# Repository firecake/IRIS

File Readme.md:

This is a try to build an open source spectrometer...

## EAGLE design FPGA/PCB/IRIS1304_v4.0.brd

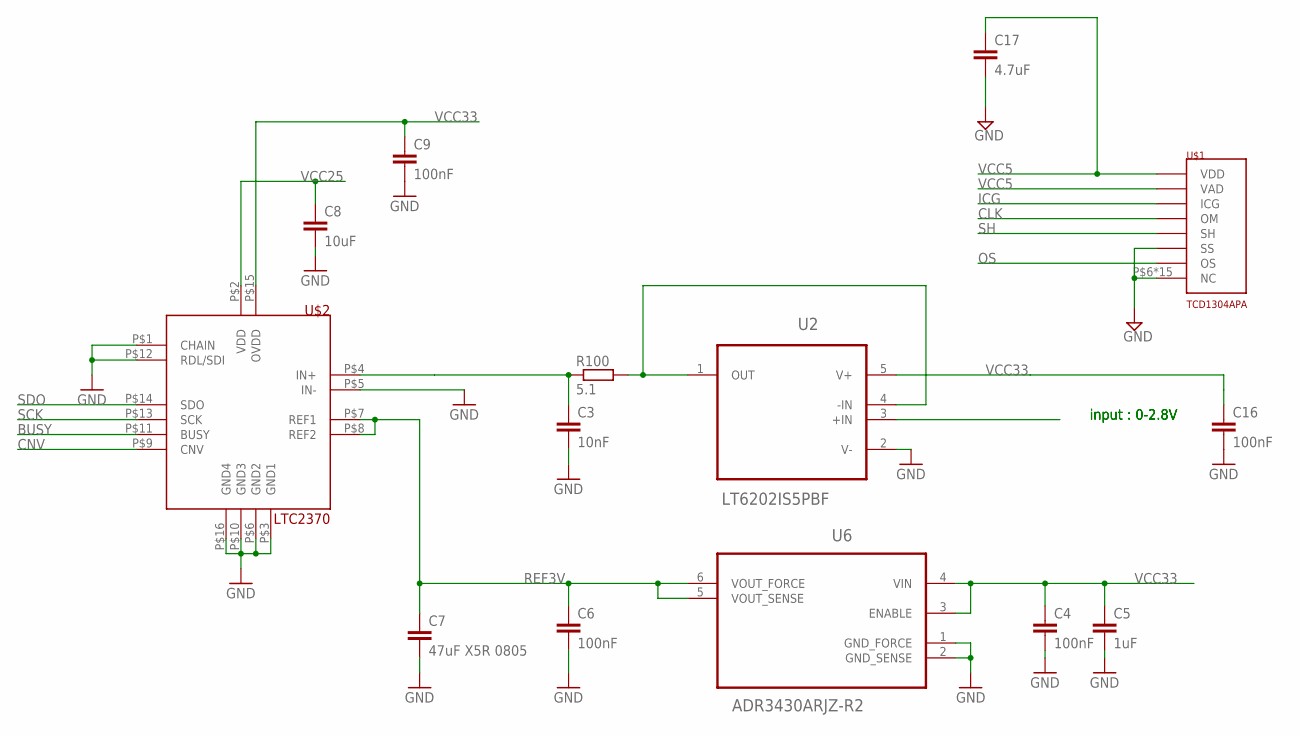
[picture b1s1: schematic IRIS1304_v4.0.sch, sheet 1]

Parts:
C3: 10nF; C0603; MPN 06035G103ZAT2A
C4, C6, C9, C16: 100nF; C0603; MPN 06033G104ZAT2A
C5: 1uF; C0603; MPN C0603C105K3PACTU
C7: 47uF X5R 0805; C0805; MPN C0805C476M9PACTU
C8: 10uF; C0603; MPN C0603C106M9PACTU
C17: 4.7uF; C0603; MPN CC0603KRX5R6BB475
R100: 5.1; R0603; MPN CRCW06035R10FNEA
U2: LT6202IS5PBF; SOT95P280X100-5N
U6: ADR3430ARJZ-R2; SOT95P280X145-6N
U$1: TCD1304APA; ILX511
U$2: LTC2370; MSOP-16; MPN LTC2370CMS-16

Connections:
BUSY: U$2.P$11 (BUSY); also elsewhere on the board
CLK: U$1.P$4 (OM); also elsewhere on the board
CNV: U$2.P$9 (CNV); also elsewhere on the board
GND: C3.2, C4.2, C5.2, C6.2, C7.2, C8.2, C9.2, C16.2, C17.2, U2.2 (V-), U6.1 (GND_FORCE), U6.2 (GND_SENSE), U$1.P$6 (NC), U$1.P$7 (NC), U$1.P$8 (NC), U$1.P$9 (NC), U$1.P$10 (NC), U$1.P$11 (NC), U$1.P$12 (NC), U$1.P$13 (NC), U$1.P$14 (NC), U$1.P$15 (NC), U$1.P$16 (NC), U$1.P$17 (NC), U$1.P$18 (NC), U$1.P$19 (NC), U$1.P$20 (NC), U$1.P$22 (SS), U$2.P$1 (CHAIN), U$2.P$3 (GND1), U$2.P$5 (IN-), U$2.P$6 (GND2), U$2.P$10 (GND3), U$2.P$12 (RDL/SDI), U$2.P$16 (GND4); also elsewhere on the board
ICG: U$1.P$3 (ICG); also elsewhere on the board
unnamed: C3.1, R100.1, U$2.P$4 (IN+)
unnamed: R100.2, U2.1 (OUT), U2.4 (-IN)
OS: U2.3 (+IN), U$1.P$21 (OS)
REF3V: C6.1, C7.1, U6.5 (VOUT_SENSE), U6.6 (VOUT_FORCE), U$2.P$7 (REF1), U$2.P$8 (REF2)
SCK: U$2.P$13 (SCK); also elsewhere on the board
SDO: U$2.P$14 (SDO); also elsewhere on the board
SH: U$1.P$5 (SH); also elsewhere on the board
VCC5: C17.1, U$1.P$1 (VDD), U$1.P$2 (VAD); also elsewhere on the board
VCC25: C8.1, U$2.P$2 (VDD); also elsewhere on the board
VCC33: C4.1, C5.1, C9.1, C16.1, U2.5 (V+), U6.3 (ENABLE), U6.4 (VIN), U$2.P$15 (OVDD); also elsewhere on the board

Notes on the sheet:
input : 0-2.8V

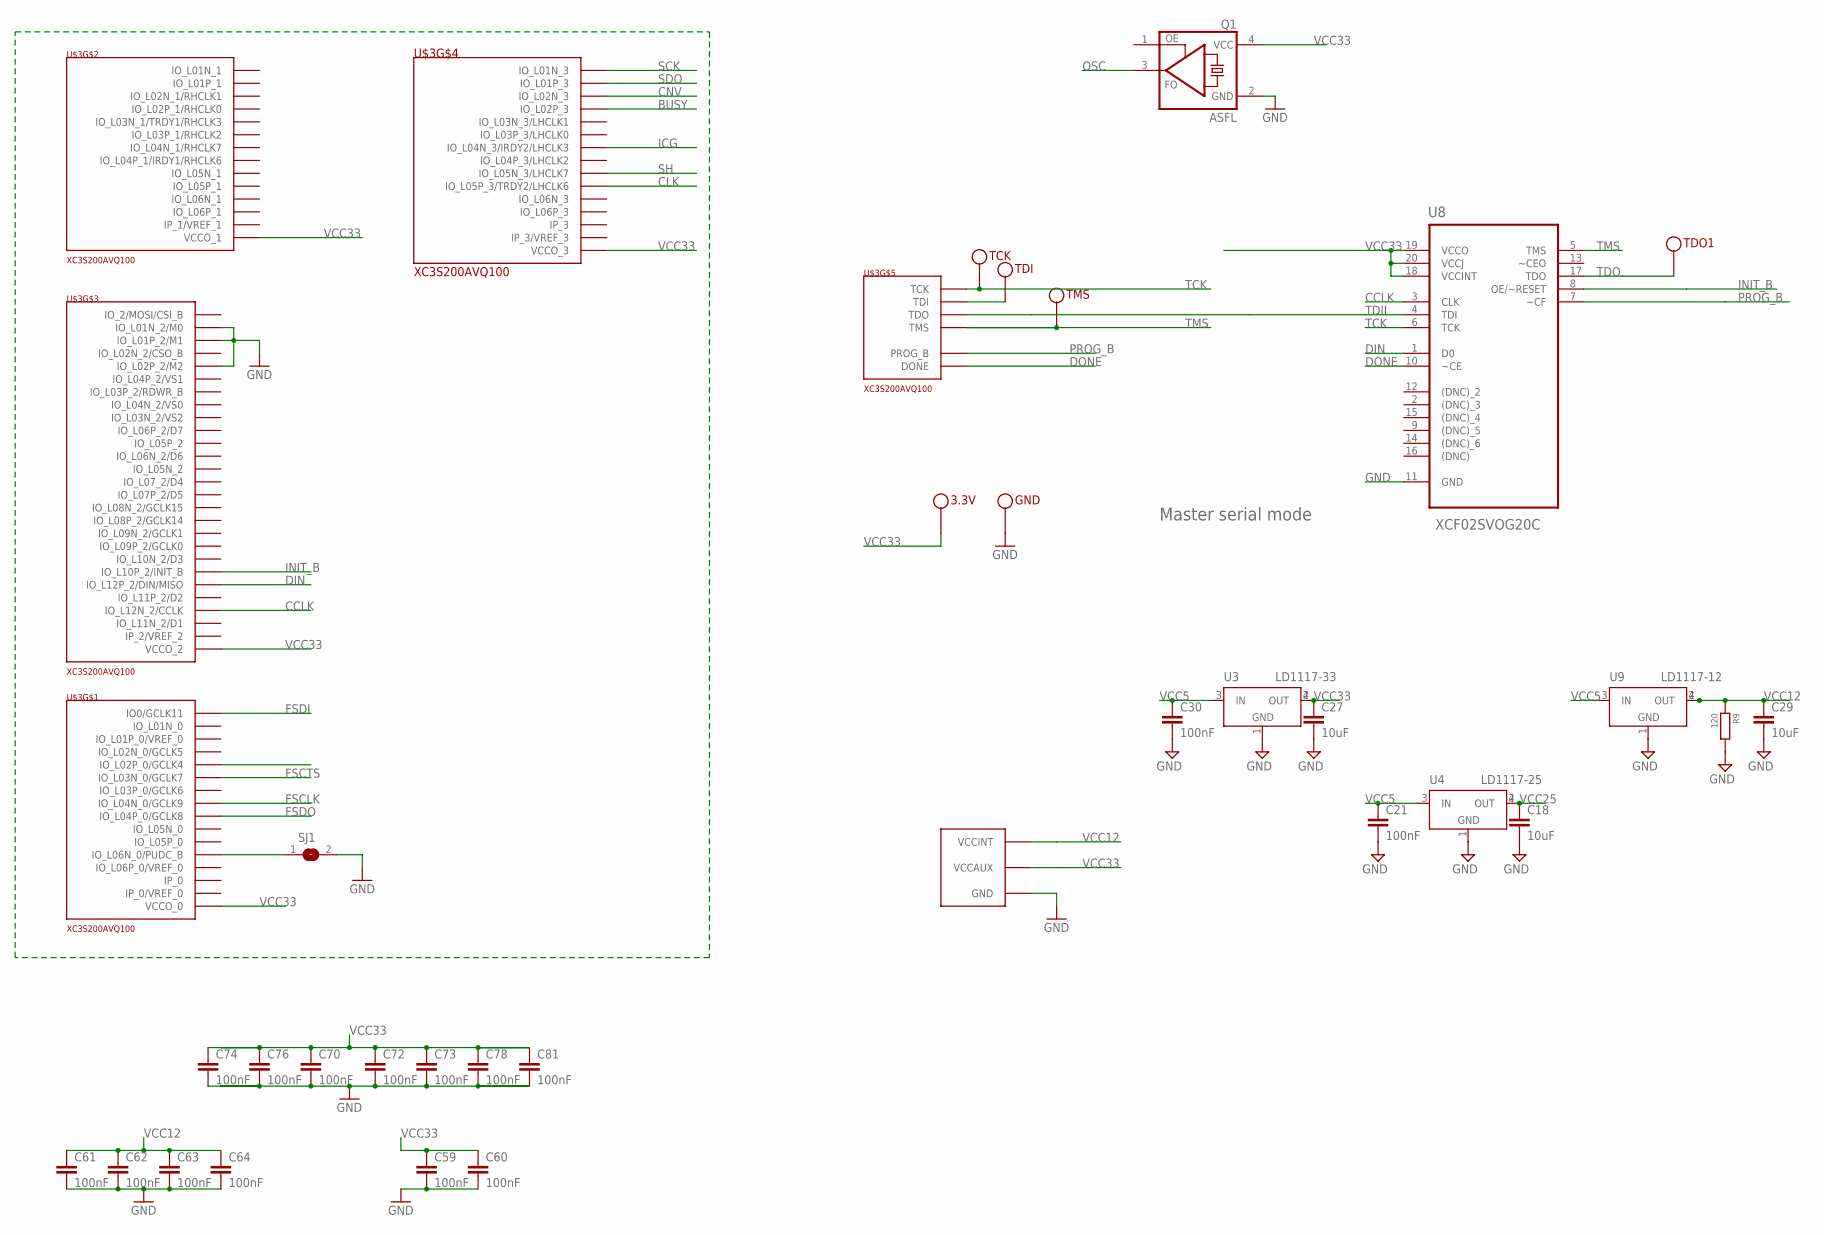
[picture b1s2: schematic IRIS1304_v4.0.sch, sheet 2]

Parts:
3.3V: TEST; MPN 001-1007-040FB9
C18, C27, C29: 10uF; C0603; MPN C0603C106M9PACTU
C21, C30, C59, C60, C61, C62, C63, C64, C70, C72, C73, C74, C76, C78, C81: 100nF; C0603; MPN 06033G104ZAT2A
GND: TEST; MPN 001-1007-040FB9
Q1: ASFL; ASF; MPN ASFL1-12.000MHZ-EK-T
R9: 120; 0805@1; MPN BMB2A0120AN1
SJ1: SJ
TCK: TEST; MPN 001-1007-040FB9
TDI: TEST; MPN 001-1007-040FB9
TDO1: TEST; MPN 001-1007-040FB9
TMS: TEST; MPN 001-1007-040FB9
U3: LD1117-33; SOT223; MPN LT1117CST-3.3#PBF
U4: LD1117-25; SOT223; MPN LD1117S25TR
U8: XCF02SVOG20C; SOP65P640X119-20N
U9: LD1117-12; SOT223; MPN LT1117IST#PBF
U$3: XC3S200AVQ100; VQ100; MPN XC3S200A-4VQG100C

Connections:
BUSY: U$3.P5 (IO_L02P_3); also elsewhere on the board
CCLK: U8.3 (CLK), U$3.P53 (IO_L12N_2/CCLK)
CLK: U$3.P15 (IO_L05P_3/TRDY2/LHCLK6); also elsewhere on the board
CNV: U$3.P6 (IO_L02N_3); also elsewhere on the board
DIN: U8.1 (D0), U$3.P51 (IO_L12P_2/DIN/MISO)
DONE: U8.10 (~CE), U$3.P54 (DONE)
FSCLK: U$3.P89 (IO_L04N_0/GCLK9); also elsewhere on the board
FSCTS: U$3.P86 (IO_L03N_0/GCLK7); also elsewhere on the board
FSDI: U$3.P90 (IO0/GCLK11); also elsewhere on the board
FSDO: U$3.P88 (IO_L04P_0/GCLK8); also elsewhere on the board
GND: C18.2, C21.2, C27.2, C29.2, C30.2, C59.2, C60.2, C61.2, C62.2, C63.2, C64.2, C70.2, C72.2, C73.2, C74.2, C76.2, C78.2, C81.2, GND.P$1, Q1.2 (GND), R9.2, SJ1.2, U3.1 (GND), U4.1 (GND), U8.11 (GND), U9.1 (GND), U$3.P8 (GND), U$3.P14 (GND), U$3.P18 (GND), U$3.P23 (IO_L01P_2/M1), U$3.P24 (IO_L02P_2/M2), U$3.P25 (IO_L01N_2/M0), U$3.P42 (GND), U$3.P47 (GND), U$3.P58 (GND), U$3.P63 (GND), U$3.P69 (GND), U$3.P74 (GND), U$3.P80 (GND), U$3.P87 (GND), U$3.P91 (GND), U$3.P95 (GND); also elsewhere on the board
ICG: U$3.P13 (IO_L04N_3/IRDY2/LHCLK3); also elsewhere on the board
INIT_B: U8.8 (OE/~RESET), U$3.P48 (IO_L10P_2/INIT_B)
unnamed: SJ1.1, U$3.P99 (IO_L06N_0/PUDC_B)
OSC: Q1.3 (FO), U$3.P83 (IO_L02P_0/GCLK4)
PROG_B: U8.7 (~CF), U$3.P100 (PROG_B)
SCK: U$3.P4 (IO_L01N_3); also elsewhere on the board
SDO: U$3.P3 (IO_L01P_3); also elsewhere on the board
SH: U$3.P16 (IO_L05N_3/LHCLK7); also elsewhere on the board
TCK: TCK.P$1, U8.6 (TCK), U$3.P76 (TCK)
TDI: TDI.P$1, U$3.P2 (TDI)
TDII: U8.4 (TDI), U$3.P75 (TDO)
TDO: TDO1.P$1, U8.17 (TDO)
TMS: TMS.P$1, U8.5 (TMS), U$3.P1 (TMS)
VCC5: C21.1, C30.1, U3.3 (IN), U4.3 (IN), U9.3 (IN); also elsewhere on the board
VCC12: C29.1, C61.1, C62.1, C63.1, C64.1, R9.1, U9.2 (OUT), U9.4 (OUT), U$3.P17 (VCCINT), U$3.P38 (VCCINT), U$3.P66 (VCCINT), U$3.P81 (VCCINT)
VCC25: C18.1, U4.2 (OUT), U4.4 (OUT); also elsewhere on the board
VCC33: 3.3V.P$1, C27.1, C59.1, C60.1, C70.1, C72.1, C73.1, C74.1, C76.1, C78.1, C81.1, Q1.4 (VCC), U3.2 (OUT), U3.4 (OUT), U8.18 (VCCINT), U8.19 (VCCO), U8.20 (VCCJ), U$3.P11 (VCCO_3), U$3.P22 (VCCAUX), U$3.P26 (VCCO_2), U$3.P45 (VCCO_2), U$3.P55 (VCCAUX), U$3.P67 (VCCO_1), U$3.P79 (VCCO_0), U$3.P92 (VCCAUX), U$3.P96 (VCCO_0); also elsewhere on the board

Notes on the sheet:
Master serial mode

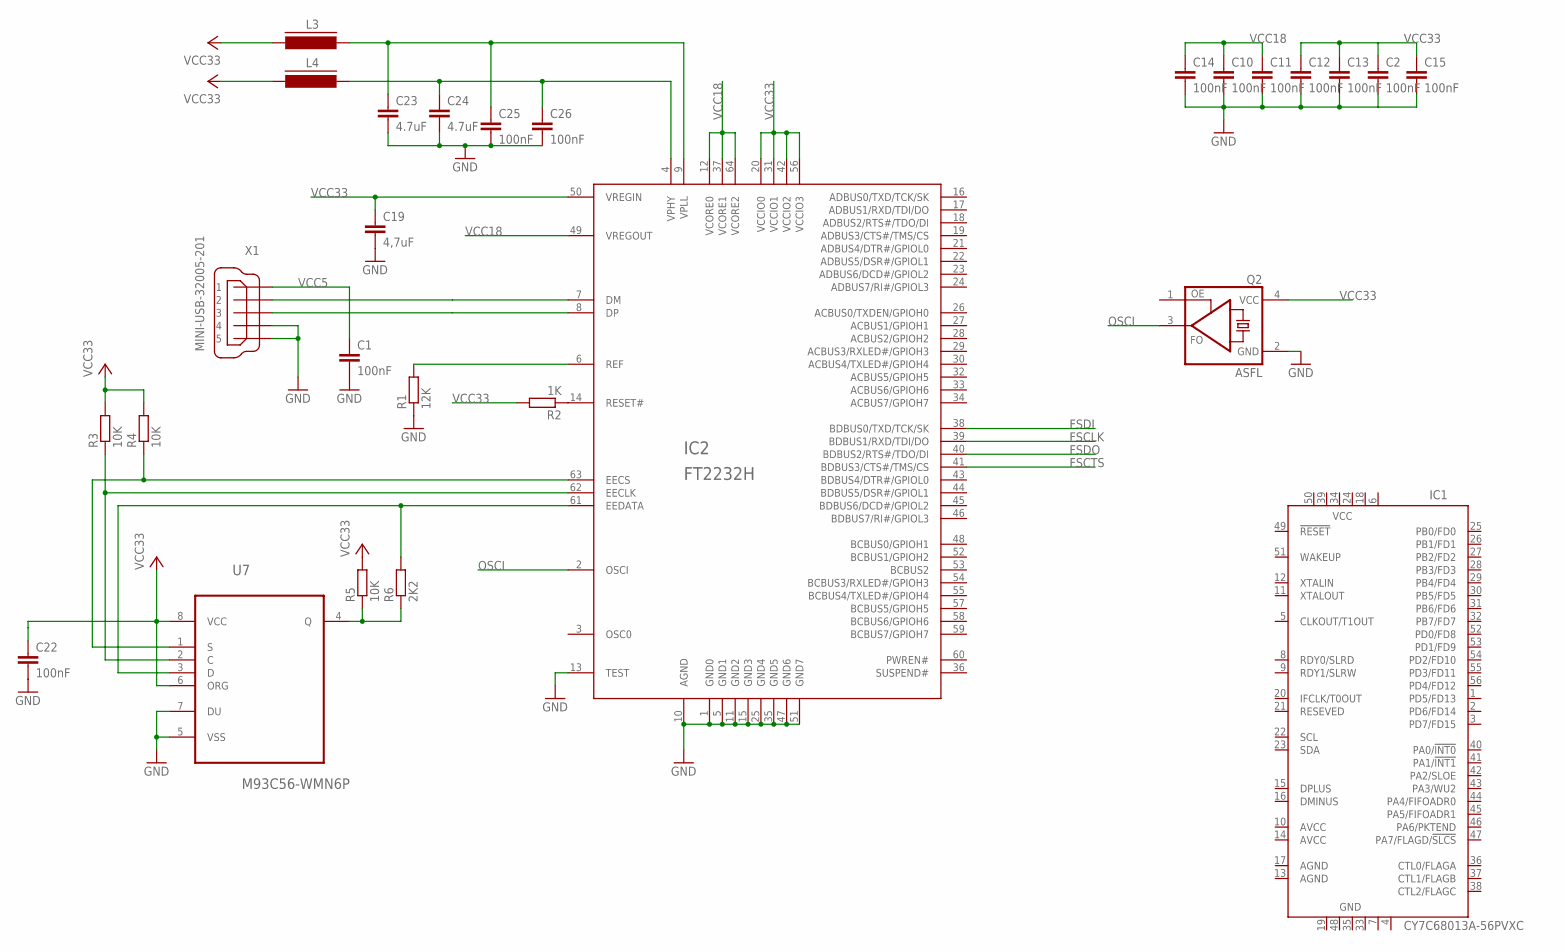
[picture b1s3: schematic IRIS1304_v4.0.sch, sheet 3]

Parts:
C1, C2, C10, C11, C12, C13, C14, C15, C22, C25, C26: 100nF; C0603; MPN 06033G104ZAT2A
C19: 4,7uF; C0805; MPN 0805ZD335KAT2A
C23, C24: 4.7uF; C0603; MPN CC0603KRX5R6BB475
IC1: CY7C68013A-56PVXC; SSOP56
IC2: FT2232H; LQFP64; MPN FT2232HL-R
L3, L4: FERRITE_BEAD805; FB805
Q2: ASFL; ASF; MPN ASFL1-12.000MHZ-EK-T
R1: 12K; R0603; MPN CPF0201D12K1C1
R2: 1K; R0603; MPN CRCW06031K00FKEA
R3, R4, R5: 10K; R0603; MPN CPF0603F10KC1
R6: 2K2; R0603; MPN ERJP03F2201V
U7: M93C56-WMN6P; SOIC127P600X175-8N
X1: MINI-USB-32005-201; 32005-201; MPN 65100516121

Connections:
D+: IC2.8 (DP), X1.3
D-: IC2.7 (DM), X1.2
FSCLK: IC2.39 (BDBUS1/RXD/TDI/DO); also elsewhere on the board
FSCTS: IC2.41 (BDBUS3/CTS#/TMS/CS); also elsewhere on the board
FSDI: IC2.38 (BDBUS0/TXD/TCK/SK); also elsewhere on the board
FSDO: IC2.40 (BDBUS2/RTS#/TDO/DI); also elsewhere on the board
GND: C1.2, C2.2, C10.2, C11.2, C12.2, C13.2, C14.2, C15.2, C19.2, C22.2, C23.2, C24.2, C25.2, C26.2, IC2.1 (GND0), IC2.5 (GND1), IC2.10 (AGND), IC2.11 (GND2), IC2.13 (TEST), IC2.15 (GND3), IC2.25 (GND4), IC2.35 (GND5), IC2.47 (GND6), IC2.51 (GND7), Q2.2 (GND), R1.1, U7.5 (VSS), U7.7 (DU), X1.4, X1.5; also elsewhere on the board
unnamed: IC2.6 (REF), R1.2
unnamed: R5.1, R6.1, U7.4 (Q)
unnamed: IC2.61 (EEDATA), R6.2, U7.3 (D)
unnamed: IC2.63 (EECS), R4.1, U7.1 (S)
unnamed: IC2.62 (EECLK), R3.1, U7.2 (C)
unnamed: C24.1, C26.1, IC2.4 (VPHY), L4.1
unnamed: C23.1, C25.1, IC2.9 (VPLL), L3.1
unnamed: IC2.14 (RESET#), R2.1
OSCI: IC2.2 (OSCI), Q2.3 (FO)
VCC5: C1.1, X1.1; also elsewhere on the board
VCC18: C10.1, C11.1, C14.1, IC2.12 (VCORE0), IC2.37 (VCORE1), IC2.49 (VREGOUT), IC2.64 (VCORE2)
VCC33: C2.1, C12.1, C13.1, C15.1, C19.1, C22.1, IC2.20 (VCCIO0), IC2.31 (VCCIO1), IC2.42 (VCCIO2), IC2.50 (VREGIN), IC2.56 (VCCIO3), L3.2, L4.2, Q2.4 (VCC), R2.2, R3.2, R4.2, R5.2, U7.6 (ORG), U7.8 (VCC); also elsewhere on the board

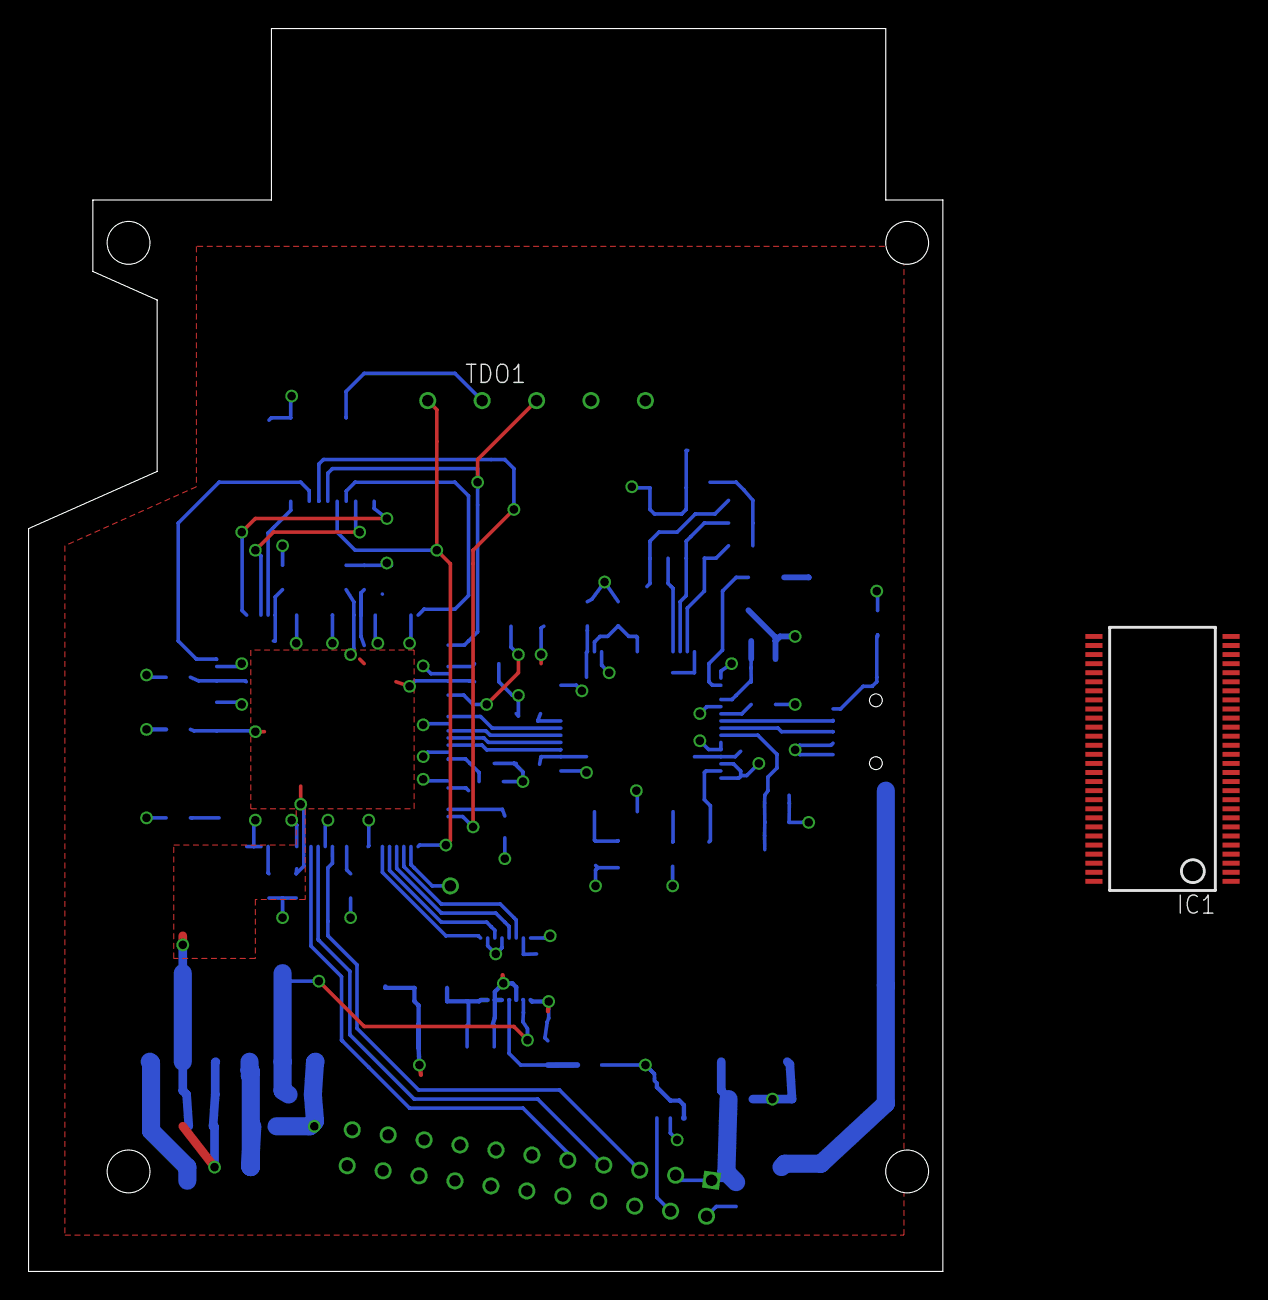
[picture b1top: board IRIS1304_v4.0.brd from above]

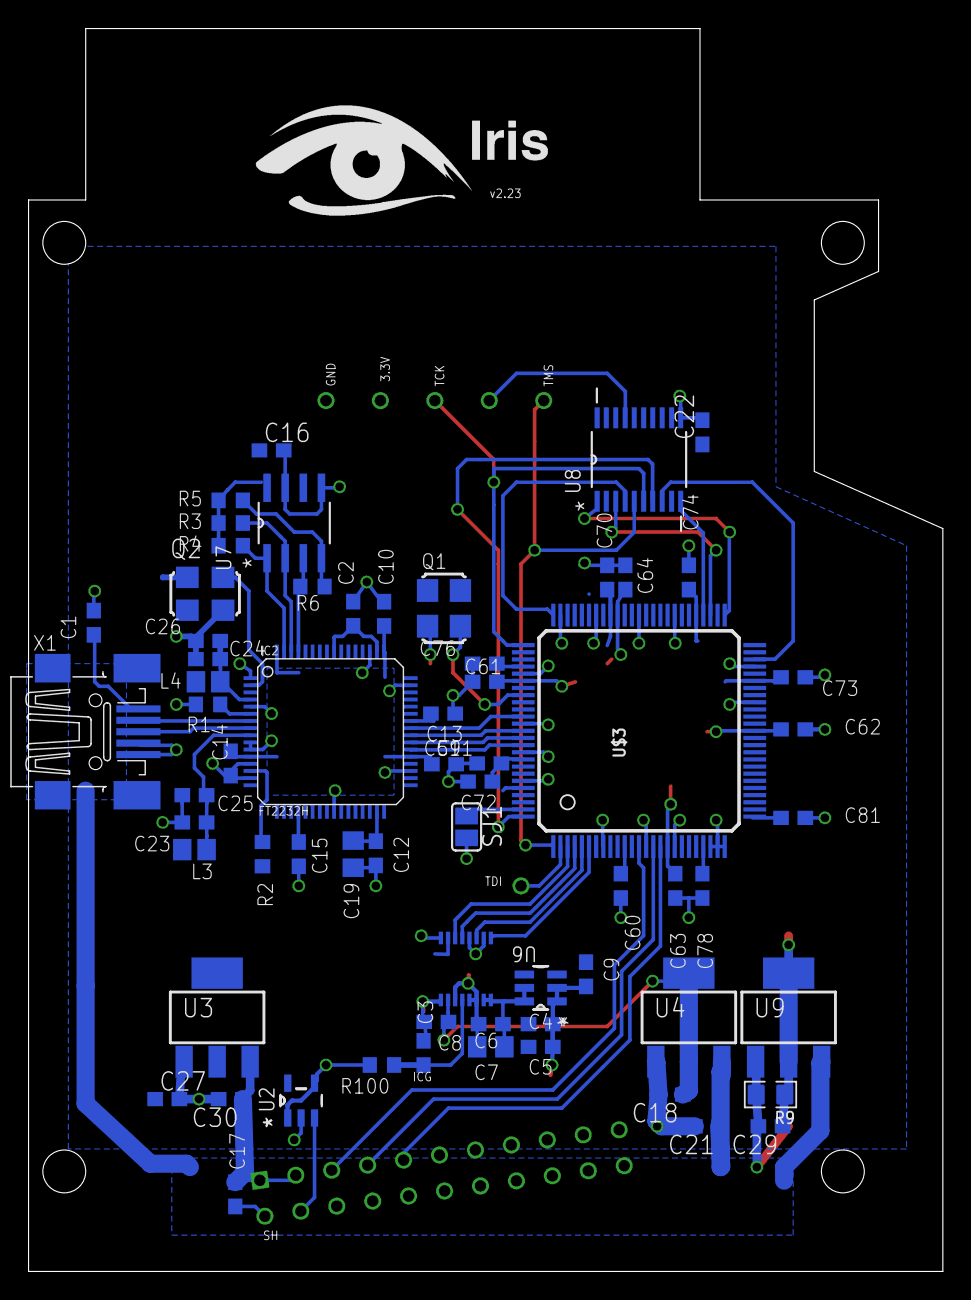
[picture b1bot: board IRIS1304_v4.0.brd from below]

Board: 2 copper layers, 64.0 x 87.0 mm, 73 parts (70 on the bottom side), 44 nets.

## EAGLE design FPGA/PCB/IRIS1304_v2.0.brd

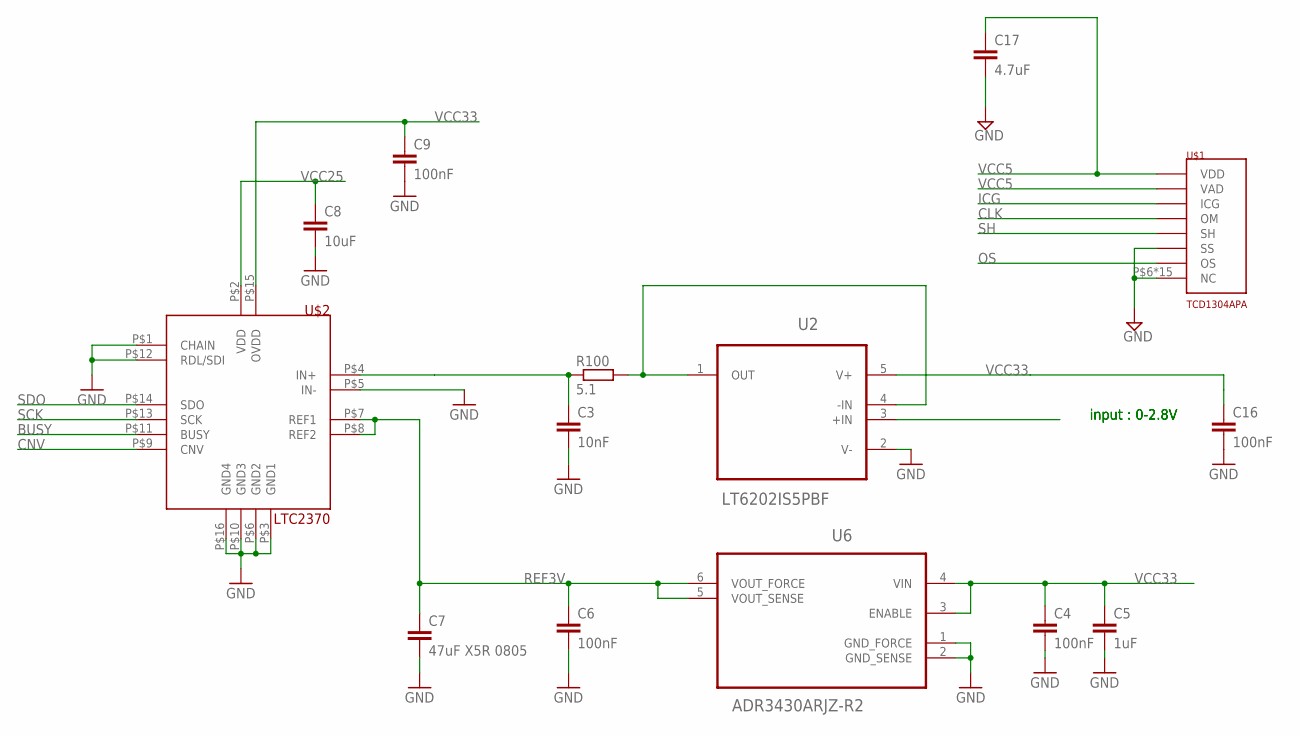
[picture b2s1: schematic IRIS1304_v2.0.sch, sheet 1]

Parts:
C3: 10nF; C0603; MPN 06035G103ZAT2A
C4, C6, C9, C16: 100nF; C0603; MPN 06033G104ZAT2A
C5: 1uF; C0603; MPN C0603C105K3PACTU
C7: 47uF X5R 0805; C0805; MPN C0805C476M9PACTU
C8: 10uF; C0603; MPN C0603C106M9PACTU
C17: 4.7uF; C0603; MPN CC0603KRX5R6BB475
R100: 5.1; R0603; MPN CRCW06035R10FNEA
U2: LT6202IS5PBF; SOT95P280X100-5N
U6: ADR3430ARJZ-R2; SOT95P280X145-6N
U$1: TCD1304APA; ILX511
U$2: LTC2370; MSOP-16; MPN LTC2370CMS-16

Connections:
BUSY: U$2.P$11 (BUSY); also elsewhere on the board
CLK: U$1.P$4 (OM); also elsewhere on the board
CNV: U$2.P$9 (CNV); also elsewhere on the board
GND: C3.2, C4.2, C5.2, C6.2, C7.2, C8.2, C9.2, C16.2, C17.2, U2.2 (V-), U6.1 (GND_FORCE), U6.2 (GND_SENSE), U$1.P$6 (NC), U$1.P$7 (NC), U$1.P$8 (NC), U$1.P$9 (NC), U$1.P$10 (NC), U$1.P$11 (NC), U$1.P$12 (NC), U$1.P$13 (NC), U$1.P$14 (NC), U$1.P$15 (NC), U$1.P$16 (NC), U$1.P$17 (NC), U$1.P$18 (NC), U$1.P$19 (NC), U$1.P$20 (NC), U$1.P$22 (SS), U$2.P$1 (CHAIN), U$2.P$3 (GND1), U$2.P$5 (IN-), U$2.P$6 (GND2), U$2.P$10 (GND3), U$2.P$12 (RDL/SDI), U$2.P$16 (GND4); also elsewhere on the board
ICG: U$1.P$3 (ICG); also elsewhere on the board
unnamed: C3.1, R100.1, U$2.P$4 (IN+)
unnamed: R100.2, U2.1 (OUT), U2.4 (-IN)
OS: U2.3 (+IN), U$1.P$21 (OS)
REF3V: C6.1, C7.1, U6.5 (VOUT_SENSE), U6.6 (VOUT_FORCE), U$2.P$7 (REF1), U$2.P$8 (REF2)
SCK: U$2.P$13 (SCK); also elsewhere on the board
SDO: U$2.P$14 (SDO); also elsewhere on the board
SH: U$1.P$5 (SH); also elsewhere on the board
VCC5: C17.1, U$1.P$1 (VDD), U$1.P$2 (VAD); also elsewhere on the board
VCC25: C8.1, U$2.P$2 (VDD); also elsewhere on the board
VCC33: C4.1, C5.1, C9.1, C16.1, U2.5 (V+), U6.3 (ENABLE), U6.4 (VIN), U$2.P$15 (OVDD); also elsewhere on the board

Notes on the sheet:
input : 0-2.8V

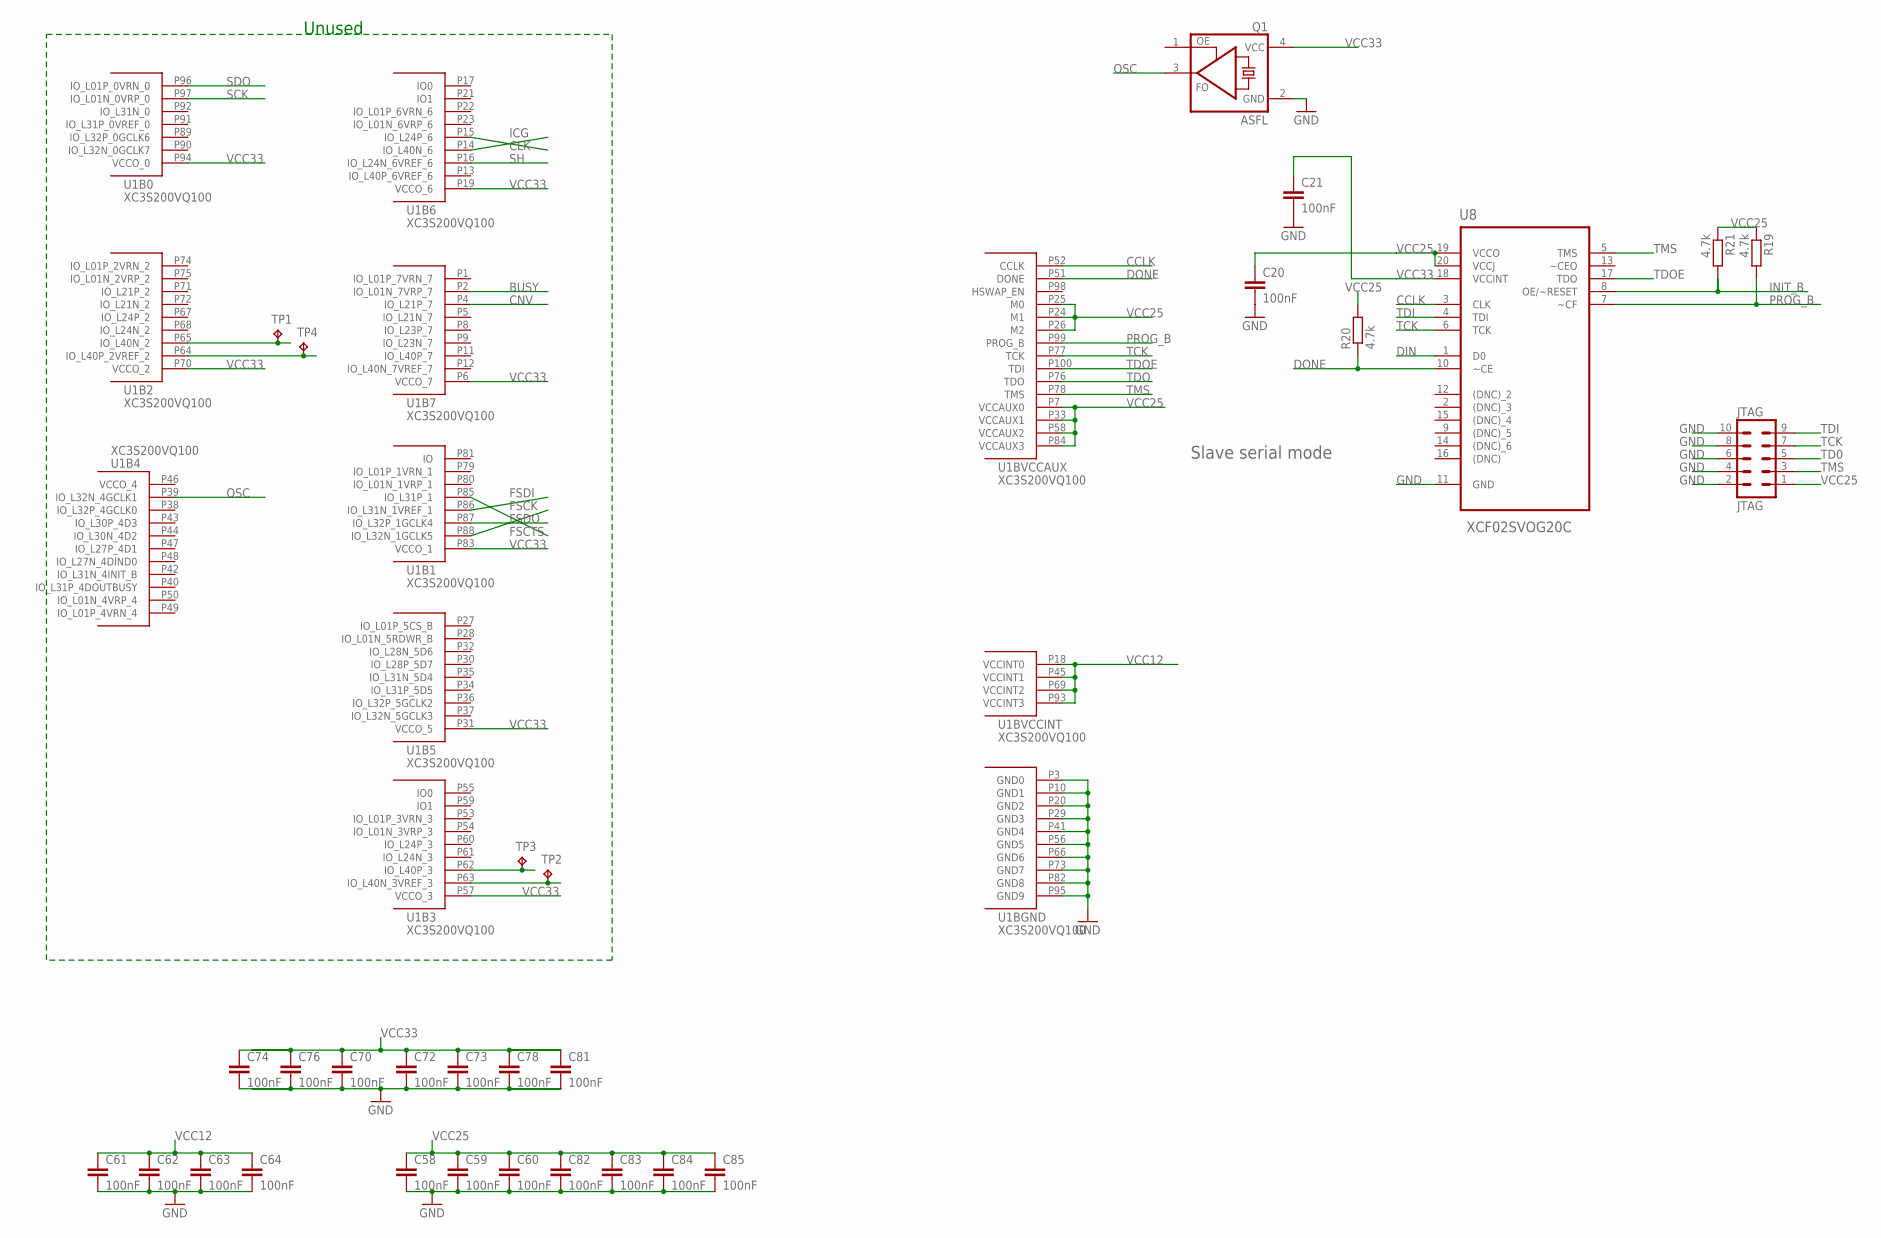
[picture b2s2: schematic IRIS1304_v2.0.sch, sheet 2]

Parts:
C20, C21, C58, C59, C60, C61, C62, C63, C64, C70, C72, C73, C74, C76, C78, C81, C82, C83, C84, C85: 100nF; C0603; MPN 06033G104ZAT2A
JTAG: JTAG; ML10; MPN TFML-105-01-S-D-RA
Q1: ASFL; ASF; MPN ASFL1-12.000MHZ-EK-T
R19, R20, R21: 4.7k; R0603; MPN CRCW06034K70FKEA
TP1, TP2, TP3, TP4: TPB1,27; B1,27
U1: XC3S200VQ100; VQ100; MPN XC3S200A-4VQG100C
U8: XCF02SVOG20C; SOP65P640X119-20N

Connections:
BUSY: U1.P2 (IO_L01N_7VRP_7); also elsewhere on the board
CCLK: U1.P52 (CCLK), U8.3 (CLK)
CLK: U1.P15 (IO_L24P_6); also elsewhere on the board
CNV: U1.P4 (IO_L21P_7); also elsewhere on the board
DIN: U8.1 (D0)
DONE: R20.1, U1.P51 (DONE), U8.10 (~CE)
FSCK: U1.P88 (IO_L32N_1GCLK5); also elsewhere on the board
FSCTS: U1.P85 (IO_L31P_1); also elsewhere on the board
FSDI: U1.P86 (IO_L31N_1VREF_1); also elsewhere on the board
FSDO: U1.P87 (IO_L32P_1GCLK4); also elsewhere on the board
GND: C20.2, C21.2, C58.2, C59.2, C60.2, C61.2, C62.2, C63.2, C64.2, C70.2, C72.2, C73.2, C74.2, C76.2, C78.2, C81.2, C82.2, C83.2, C84.2, C85.2, JTAG.2, JTAG.4, JTAG.6, JTAG.8, JTAG.10, Q1.2 (GND), U1.P3 (GND0), U1.P10 (GND1), U1.P20 (GND2), U1.P29 (GND3), U1.P41 (GND4), U1.P56 (GND5), U1.P66 (GND6), U1.P73 (GND7), U1.P82 (GND8), U1.P95 (GND9), U8.11 (GND); also elsewhere on the board
ICG: U1.P14 (IO_L40N_6); also elsewhere on the board
INIT_B: R21.2, U8.8 (OE/~RESET)
unnamed: TP2.TP, U1.P63 (IO_L40N_3VREF_3)
unnamed: TP4.TP, U1.P64 (IO_L40P_2VREF_2)
unnamed: TP3.TP, U1.P62 (IO_L40P_3)
unnamed: TP1.TP, U1.P65 (IO_L40N_2)
OSC: Q1.3 (FO), U1.P39 (IO_L32N_4GCLK1)
PROG_B: R19.2, U1.P99 (PROG_B), U8.7 (~CF)
SCK: U1.P97 (IO_L01N_0VRP_0); also elsewhere on the board
SDO: U1.P96 (IO_L01P_0VRN_0); also elsewhere on the board
SH: U1.P16 (IO_L24N_6VREF_6); also elsewhere on the board
TCK: JTAG.7, U1.P77 (TCK), U8.6 (TCK)
TD0: JTAG.5
TDI: JTAG.9, U8.4 (TDI)
TDO: U1.P76 (TDO)
TDOE: U1.P100 (TDI), U8.17 (TDO)
TMS: JTAG.3, U1.P78 (TMS), U8.5 (TMS)
VCC12: C61.1, C62.1, C63.1, C64.1, U1.P18 (VCCINT0), U1.P45 (VCCINT1), U1.P69 (VCCINT2), U1.P93 (VCCINT3); also elsewhere on the board
VCC25: C20.1, C58.1, C59.1, C60.1, C82.1, C83.1, C84.1, C85.1, JTAG.1, R19.1, R20.2, R21.1, U1.P7 (VCCAUX0), U1.P24 (M1), U1.P25 (M0), U1.P26 (M2), U1.P33 (VCCAUX1), U1.P58 (VCCAUX2), U1.P84 (VCCAUX3), U8.19 (VCCO), U8.20 (VCCJ); also elsewhere on the board
VCC33: C21.1, C70.1, C72.1, C73.1, C74.1, C76.1, C78.1, C81.1, Q1.4 (VCC), U1.P6 (VCCO_7), U1.P19 (VCCO_6), U1.P31 (VCCO_5), U1.P57 (VCCO_3), U1.P70 (VCCO_2), U1.P83 (VCCO_1), U1.P94 (VCCO_0), U8.18 (VCCINT); also elsewhere on the board

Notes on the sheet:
Unused
Slave serial mode

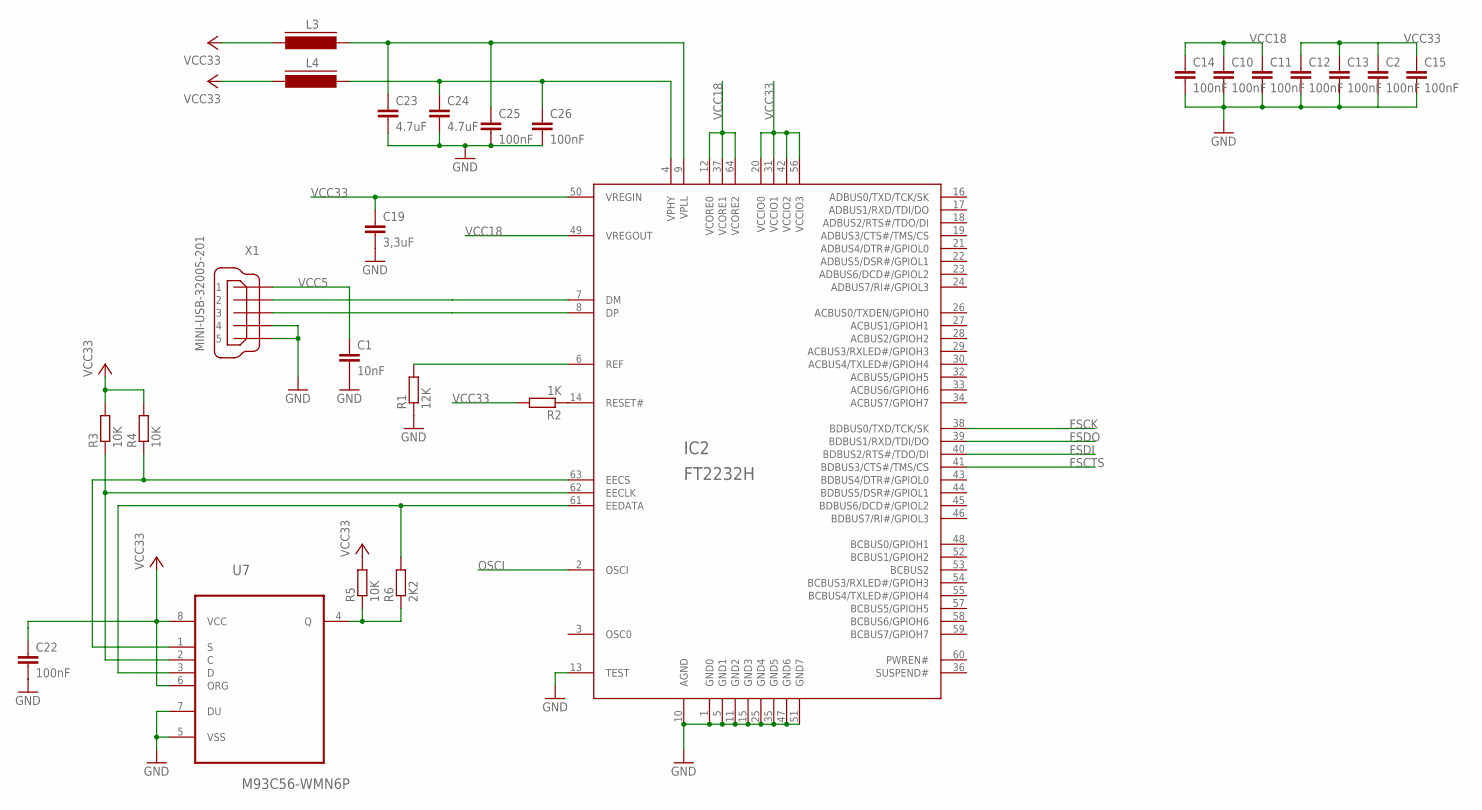
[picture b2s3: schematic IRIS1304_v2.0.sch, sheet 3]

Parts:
C1: 10nF; C0603; MPN 06035G103ZAT2A
C2, C10, C11, C12, C13, C14, C15, C22, C25, C26: 100nF; C0603; MPN 06033G104ZAT2A
C19: 3,3uF; C0805; MPN 0805ZD335KAT2A
C23, C24: 4.7uF; C0603; MPN CC0603KRX5R6BB475
IC2: FT2232H; LQFP64; MPN FT2232HL-R
L3, L4: FERRITE_BEAD805; FB805
R1: 12K; R0603; MPN CPF0201D12K1C1
R2: 1K; R0603; MPN CRCW06031K00FKEA
R3, R4, R5: 10K; R0603; MPN CPF0603F10KC1
R6: 2K2; R0603; MPN ERJP03F2201V
U7: M93C56-WMN6P; SOIC127P600X175-8N
X1: MINI-USB-32005-201; 32005-201; MPN 65100516121

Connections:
D+: IC2.8 (DP), X1.3
D-: IC2.7 (DM), X1.2
FSCK: IC2.38 (BDBUS0/TXD/TCK/SK); also elsewhere on the board
FSCTS: IC2.41 (BDBUS3/CTS#/TMS/CS); also elsewhere on the board
FSDI: IC2.40 (BDBUS2/RTS#/TDO/DI); also elsewhere on the board
FSDO: IC2.39 (BDBUS1/RXD/TDI/DO); also elsewhere on the board
GND: C1.2, C2.2, C10.2, C11.2, C12.2, C13.2, C14.2, C15.2, C19.2, C22.2, C23.2, C24.2, C25.2, C26.2, IC2.1 (GND0), IC2.5 (GND1), IC2.10 (AGND), IC2.11 (GND2), IC2.13 (TEST), IC2.15 (GND3), IC2.25 (GND4), IC2.35 (GND5), IC2.47 (GND6), IC2.51 (GND7), R1.1, U7.5 (VSS), U7.7 (DU), X1.4, X1.5; also elsewhere on the board
unnamed: IC2.6 (REF), R1.2
unnamed: R5.1, R6.1, U7.4 (Q)
unnamed: IC2.61 (EEDATA), R6.2, U7.3 (D)
unnamed: IC2.63 (EECS), R4.1, U7.1 (S)
unnamed: IC2.62 (EECLK), R3.1, U7.2 (C)
unnamed: C24.1, C26.1, IC2.4 (VPHY), L4.1
unnamed: C23.1, C25.1, IC2.9 (VPLL), L3.1
unnamed: IC2.14 (RESET#), R2.1
OSCI: IC2.2 (OSCI)
VCC5: C1.1, X1.1; also elsewhere on the board
VCC18: C10.1, C11.1, C14.1, IC2.12 (VCORE0), IC2.37 (VCORE1), IC2.49 (VREGOUT), IC2.64 (VCORE2)
VCC33: C2.1, C12.1, C13.1, C15.1, C19.1, C22.1, IC2.20 (VCCIO0), IC2.31 (VCCIO1), IC2.42 (VCCIO2), IC2.50 (VREGIN), IC2.56 (VCCIO3), L3.2, L4.2, R2.2, R3.2, R4.2, R5.2, U7.6 (ORG), U7.8 (VCC); also elsewhere on the board

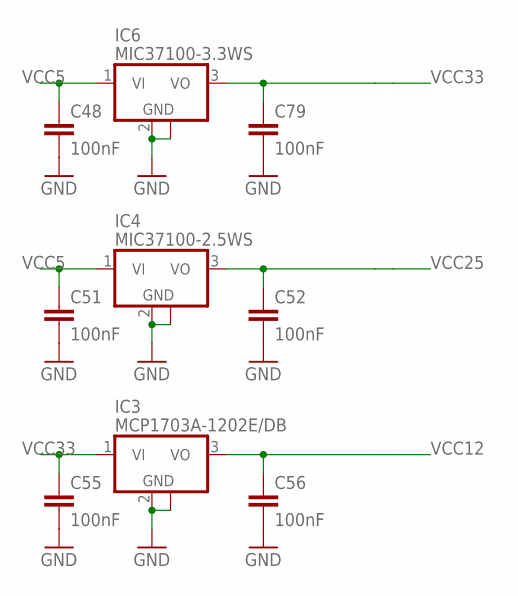
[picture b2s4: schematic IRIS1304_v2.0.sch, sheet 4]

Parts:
C48, C51, C52, C55, C56, C79: 100nF; C0603; MPN 06033G104ZAT2A
IC3: MCP1703A-1202E/DB; SOT223; MPN MCP1703A-1202E/DB
IC4: MIC37100-2.5WS; SOT223; MPN MIC37100-2.5WS TR
IC6: MIC37100-3.3WS; SOT223; MPN MIC37100-3.3WS

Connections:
GND: C48.2, C51.2, C52.2, C55.2, C56.2, C79.2, IC3.2 (GND), IC3.4 (GND), IC4.2 (GND), IC4.4 (GND), IC6.2 (GND), IC6.4 (GND); also elsewhere on the board
VCC5: C48.1, C51.1, IC4.1 (VI), IC6.1 (VI); also elsewhere on the board
VCC12: C56.1, IC3.3 (VO); also elsewhere on the board
VCC25: C52.1, IC4.3 (VO); also elsewhere on the board
VCC33: C55.1, C79.1, IC3.1 (VI), IC6.3 (VO); also elsewhere on the board
